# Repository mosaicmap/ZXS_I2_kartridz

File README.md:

# ZXS_I2_kartridz

Simple ROM cartridge for [Sinclair ZX Interface 2](https://en.wikipedia.org/wiki/ZX_Interface_2).

**This is basically updated Droy's [ZX Cart](http://trastero.speccy.org/cosas/droy/cartuchos/cartuchos_s.htm)**. My version contains an EEPROM chip **W27C512** instead of the 27\*128 or 27\*256. The main reason is that the W27C512 is more common and cheaper than 27\*128 and 27\*256 chips nowadays (Search for W27C512 on eBay...) W27C512 has also a bigger capacity. One cartridge can hold up to four 16 KiB ROM banks. Of course, only one ROM file can be active at one time.  

## Notes 

A HW programmer is required for uploading the ROM file to the EEPROM chip. For example, a relatively cheap universal programmer *MiniPro TL866CS* or *MiniPro TL866 II* from eBay is sufficient. Another option may be a homemade EEPROM programmer made of an Arduino; check for example [eeprom_programmer by StormTrooper](https://github.com/StormTrooper/eeprom_programmer) and similar projects.

To simplify ROMs upload it is possible concat four ROM files to a single file. Command under Linux/Unix: ``cat 1.rom 2.rom 3.rom 4.rom > myCompilation.rom``; under Windows/MS-DOS: ``copy /b 1.rom + 2.rom + 3.rom + 4.rom myCompilation.rom``

Jumpers A14 and A15 decide which 16 KiB ROM bank is active. (A14 and A15 are address pins of the W27C512, not A14 and A15 of the ZX Spectrum Edge connector)

This is only a simple ROM cartridge for 16 KiB ROMs. If you want a better cartridge, check for example sophisticated [Paul Farrow's ZXC4 cartridge](http://www.fruitcake.plus.com/Sinclair/Interface2/Cartridges/Interface2_RC_ZXC4.htm)

## EAGLE project

The project contains: schematic ``ZXS_I2_kartridz.sch`` and board ``ZXS_I2_kartridz.brd``. Also ``lbr/zxs_i2_rom_edge_connector.lbr`` is required.

It was created with a freeware version of Autodesk EAGLE.

## ROMs

See nice [overview by Paul Farrow](http://www.fruitcake.plus.com/Sinclair/Interface2/Cartridges/Interface2_RC_Cartridges.htm)

### Officialy released games (1984)

Originaly was released only 10 games. Namely:

- Backgammon
- Cookie
- Chess
- Horace and the Spiders
- Hungry Horace
- Jetpac
- Planetoids
- PSSST
- Space Raiders
- Tranz Am

You can download all ROM files of these games as [archive carts.zip](http://trastero.speccy.org/cosas/droy/cartuchos/carts.zip)

### Unreleased prototypes (cancelled)

- Popeye
- Q*Bert
- Gyruss
- Star Wars - The Arcade Game
- Return of the Jedi - Death Star Battle
- Loco Motion
- Montezuma's Revenge

### Sinclair BASIC for ZX Spectrum (1982) 

### Alternative BASIC interpreters

- OpenSE BASIC (mirrors: [worldofspectrum](https://worldofspectrum.org/archive/software/utilities/opense-basic-andrew-s-owen), [spectrumcomputing](https://spectrumcomputing.co.uk/entry/27510/ZX-Spectrum/OpenSE_BASIC))
- Gosh Woderful BASIC by Geoff Wearmouth ([mirror](https://8bit.yarek.pl/upgrade/zx.roms/gw03.zip))
- [Busy Soft ROM](https://busy.speccy.cz/tvorba/zxromky.htm)
- [prettybasic](https://github.com/reclaimed/prettybasic)
- ...

### Diagnostics 

Very useful ROMs for testing hardware of the ZX Spectrum.

- [Retroleum Diag ROM](http://blog.retroleum.co.uk/smart.zip) 
- [ZX-Diagnostics ROM by Brendan Alford](https://github.com/brendanalford/zx-diagnostics/releases)

### Experimental games

- DeathStar (8 KiB) (See [on fruitcake.plus.com](http://www.fruitcake.plus.com/Sinclair/Interface2/Cartridges/Interface2_RC_New_3rdParty_DeathStar.htm))

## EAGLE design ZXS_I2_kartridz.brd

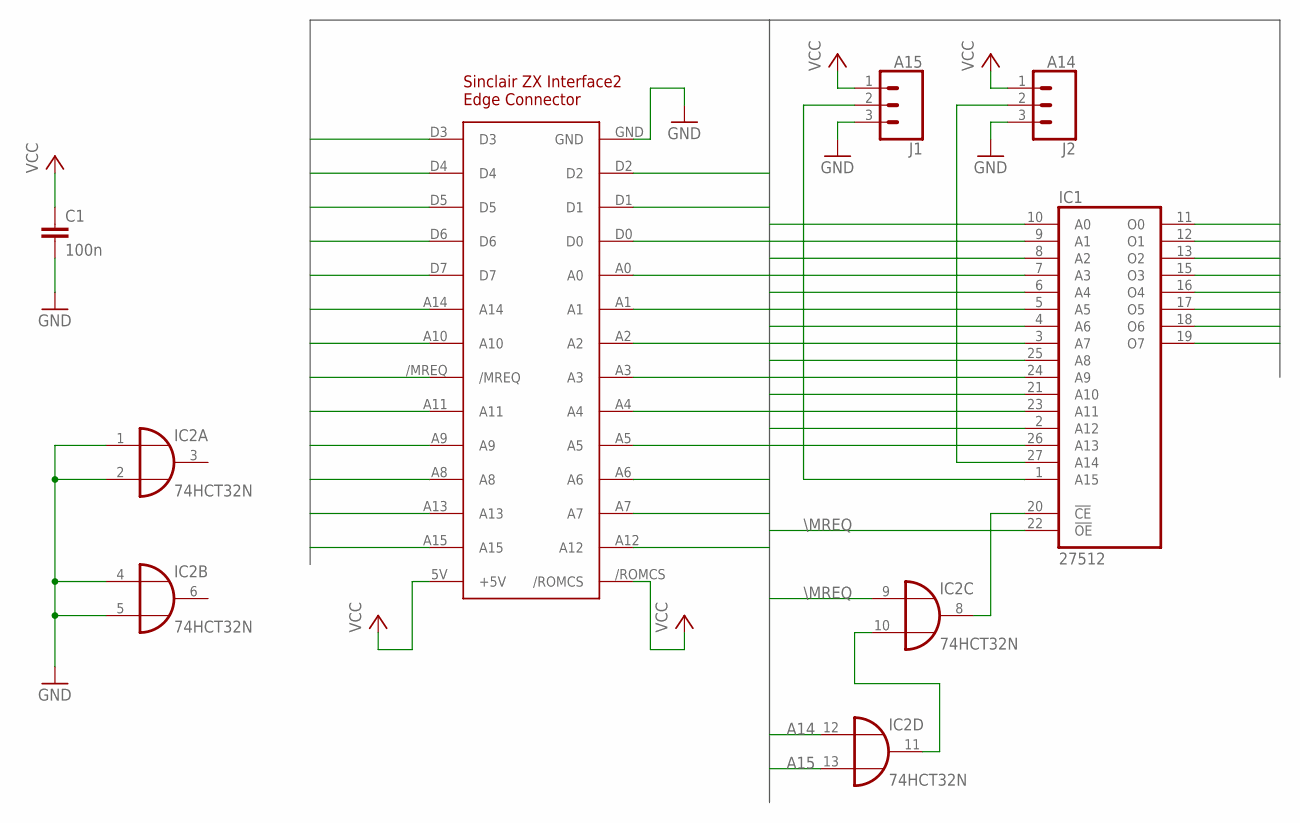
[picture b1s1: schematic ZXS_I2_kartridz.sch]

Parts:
C1: 100n; C050-024X044
IC1: 27512; DIL28
IC2: 74HCT32N; DIL14
J1: A15; 1X03
J2: A14; 1X03
U$1: ZX_I2_ROM_EDGE_CONNECTOR; ZX_I2_ROM_EDGE_CONNECTOR_V2

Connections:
A0: IC1.10 (A0), U$1.A0
A1: IC1.9 (A1), U$1.A1
A2: IC1.8 (A2), U$1.A2
A3: IC1.7 (A3), U$1.A3
A4: IC1.6 (A4), U$1.A4
A5: IC1.5 (A5), U$1.A5
A6: IC1.4 (A6), U$1.A6
A7: IC1.3 (A7), U$1.A7
A8: IC1.25 (A8), U$1.A8
A9: IC1.24 (A9), U$1.A9
A10: IC1.21 (A10), U$1.A10
A11: IC1.23 (A11), U$1.A11
A12: IC1.2 (A12), U$1.A12
A13: IC1.26 (A13), U$1.A13
A14: IC2.12 (I0), U$1.A14
A15: IC2.13 (I1), U$1.A15
D0: IC1.11 (O0), U$1.D0
D1: IC1.12 (O1), U$1.D1
D2: IC1.13 (O2), U$1.D2
D3: IC1.15 (O3), U$1.D3
D4: IC1.16 (O4), U$1.D4
D5: IC1.17 (O5), U$1.D5
D6: IC1.18 (O6), U$1.D6
D7: IC1.19 (O7), U$1.D7
GND: C1.2, IC1.14 (GND), IC2.1 (I0), IC2.2 (I1), IC2.4 (I0), IC2.5 (I1), IC2.7 (GND), J1.3, J2.3, U$1.GND
unnamed: IC2.10 (I1), IC2.11 (O)
unnamed: IC1.27 (A14), J2.2
unnamed: IC1.20 (!CE), IC2.8 (O)
unnamed: IC1.1 (A15), J1.2
VCC: C1.1, IC1.28 (VCC), IC2.14 (VCC), J1.1, J2.1, U$1.5V (+5V), U$1./ROMCS
\MREQ: IC1.22 (!OE), IC2.9 (I0), U$1./MREQ

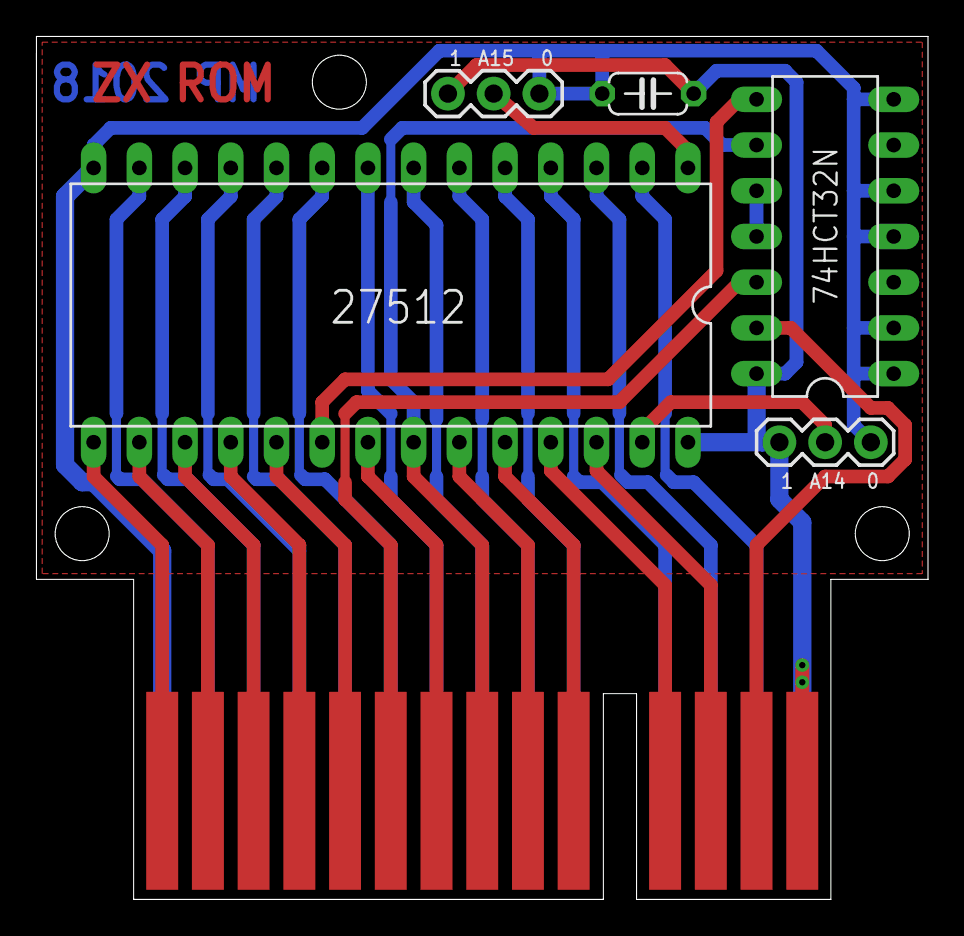
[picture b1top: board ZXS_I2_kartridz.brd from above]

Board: 2 copper layers, 49.5 x 47.9 mm, 6 parts (0 on the bottom side), 31 nets.

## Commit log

2018-06-04 readme tmp
2019-03-13 bsrom odkaz
2019-06-06 photo
2021-05-03 Update README.md
    corrections
2021-05-04 notes

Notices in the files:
parts and their libraries:
SparkFun-Connectors: Licensing: Creative Commons ShareAlike 4.0 International - https://creativecommons.org/licenses/by-sa/4.0
